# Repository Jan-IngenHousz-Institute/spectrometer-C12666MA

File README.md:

# C12666MA spectrometer

Hamamatsu C12666MA micro-spectrometer (340–780 nm, 256 pixels) read by a
Raspberry Pi Pico through an MCP3301 13-bit ADC, on the JII "C12666MA Board
v2". Includes a live GUI for chlorophyll fluorescence: it calculates relative
fluorescence from the incident-light region on a selected top spectrometer and
the fluorescence region on a selected bottom spectrometer, then plots the
ratio over time. Multiple spectrometers are synchronized for recordings of
minutes to days. A terminal recorder uploads the spectra to
an [openJII](https://openjii.org) experiment
([README_recorder.md](README_recorder.md)).

```
firmware/main.py      MicroPython firmware (copy to the Pico as main.py)
c12666ma/             Python package: driver, analysis, recorder, GUI, openJII upload and download
calibration/          pixel -> wavelength calibration and its laser measurements
tools/hw_check.py     speed / reliability / noise check of a connected board
tests/                unit tests (no hardware needed)
notebooks/            K. Tolsma's measurement and PAM notebooks, and a Digilent WaveForms test
kicad/                PCB v2, two variants: Pico on the back / on the front
legacy/arduino/       earlier Arduino Uno sketches, incl. the MCP3301 bench test
legacy/python-v1/     the first MicroPython firmware (MAIN.py) and playground notebooks
```

## Quick start

```
pip install -r requirements.txt
python -m c12666ma                 # the GUI
python -m c12666ma --simulate 3    # try it with three simulated spectrometers
```

1. Spectrometers plugged in are connected at start-up; later ones with
   **Auto-detect & connect**. Select one in the table to set its name, gain,
   integration time, averages and LED.
2. **Start**. With one spectrometer, "As fast as possible" streams one
   spectrum per integration time (about 190 spectra/s at the 5.2 ms minimum).
   Otherwise all spectrometers take one spectrum together at every period (see
   below).
3. Cover the sensors or switch the light off and press **Take dark**. The
   yield needs a dark spectrum taken with the same gain, integration time and
   averages, and the table shows when one no longer matches ("redo").
4. Drag the blue (`incident_light`) and red (`fluorescence`) regions, or type
   their limits. They apply to all spectrometers.
   Select the top (incident-light) and bottom (fluorescence) scanners in the
   controls below the live graph; both need matching dark spectra.
5. The **3D spectrum history** tab shows the most recent spectra of the
   selected spectrometer as a surface over wavelength, time and counts. It
   keeps up to 5000 spectra per spectrometer in memory, can show the latest
   2–500, and updates while it is open.
6. **Start recording**, optionally with a duration. It runs until stopped or
   for days; a new file part starts every 24 h (adjustable).

`run_C12666MA_3D_GUI.py` starts the GUI from any folder:

```
python path\to\spectrometer-C12666MA\run_C12666MA_3D_GUI.py
```

### Several spectrometers

All spectrometers take a spectrum together at every tick. The PC sends each
trigger up to 0.5 s ahead, with the start time converted to that device's
own clock. The clocks are measured every 30 s (offset and crystal drift), so
the devices should start within about a millisecond even when the PC
stalls. Spectra of the same tick have the same `seq` in every file.

- **Minimum period:** set by the slowest spectrometer, its averages ×
  integration time plus about 12 ms (readout and margins). The GUI shows
  which one.
- **Different integration times:** the windows are centred on the same
  moment; a 10 ms spectrum is taken in the middle of a 1 s one.
- **Unplugged or reset devices** are reconnected automatically (by their
  unique ID) and the recording continues; gaps show up as missed ticks.
- **Long recordings:** the PC is kept awake while recording, and the
  recording stops cleanly (with a note) if less than 500 MB of disk is left.

### Rel. fluo. yield

The live GUI calculates `bottom fluorescence / top incident_light` from
dark-subtracted sums in the selected wavelength regions. It combines readings
only when both scanners have the same synchronized frame sequence number. A
region "has signal" when its sum is more than *k* × its noise (k = 5 by
default; the noise comes from that scanner's dark frames). Both scanners need
a matching dark spectrum. The per-scanner `rel_fluo_yield` values in recording
files remain calculated from each individual spectrometer.

| Top incident_light | Bottom fluorescence | result |
|---|---|---|
| signal | any | bottom fluorescence / top incident_light |
| no signal | signal | empty + warning *fluorescence without incident light* |
| no signal | no signal | 0 |

Frames with a pixel at saturation in either region are flagged (orange in
the plot, `;saturated` in the file). The saturation level is about 3100
counts at high gain and about 1950 at low gain; both can be adjusted in the
GUI.

### Recording format

Each recording is a folder named `<name>_<date>_<time>`:

```
SIM-1_000001_part001.csv    one series per spectrometer (<name>_<end of its ID>),
SIM-1_000001_part002.csv    a new part every 24 h
SIM-2_000002_part001.csv
session.json                devices, settings, calibrations, counts, why it stopped
events.log                  connections, reconnects, settings changes, ...
```

Open a part with `pandas.read_csv(path, comment="#")`. The header lines
(`# ...`) hold the settings, regions and calibration. The `kind` column
separates the row types:

- `wavelength_nm`: the wavelength of every pixel column `px0..px255`
- `dark` / `dark_std`: the dark reference (written whenever one is taken, and
  repeated at the top of every part)
- `spectrum`: one row per spectrum, with the timestamp (start of
  integration), `t_s` (seconds since the recording started, the same time base
  for all spectrometers), `seq` (the tick number), settings, optionally
  `incident_light`, `fluorescence`, `rel_fluo_yield`, `yield_status`, and the
  raw counts (not dark-subtracted).

### Unattended recording with upload to openJII

`python -m c12666ma.record` records with all connected spectrometers from
the terminal, for hours or days, and sends the spectra to an experiment on
[openJII](https://openjii.org) as an *upload table*. Each unit keeps its own
gain, integration time and averages.

```
python -m c12666ma.record                 asks everything: sign-in, experiment, settings
python -m c12666ma.record login           (re)enter the openJII API key
python -m c12666ma.record upload FOLDER   finish the uploads of an earlier recording
python -m c12666ma.download               download all tables of an experiment into one JSON file
```

The spectra are written locally first (the recording folder described above)
and uploaded every 15 minutes, one row per spectrum with its timestamp and
settings. Without network they wait on disk and go out later.
**[README_recorder.md](README_recorder.md)** explains the whole procedure:
sign-in, laptop settings for runs of several days, the uploaded columns,
starting from Task Scheduler, downloading the data again and troubleshooting.

# Recording to openJII from the terminal

`python -m c12666ma.record` records with every C12666MA spectrometer plugged
into the laptop, one spectrum per unit at a fixed interval, for hours or days.
Each unit can have its own gain, integration time and averages. Every spectrum
is saved on the laptop first and then uploaded to an experiment on
[openJII](https://openjii.org), with its timestamp and all the settings it was
taken with.

No GUI is needed: the script asks its questions in the terminal, and remembers
the answers for the next run.

- [Before you start](#before-you-start)
- [First recording, step by step](#first-recording-step-by-step)
- [Leaving it running for days](#leaving-it-running-for-days)
- [Stopping, and finishing the uploads](#stopping-and-finishing-the-uploads)
- [What is saved](#what-is-saved)
- [Starting without questions](#starting-without-questions)
- [Troubleshooting](#troubleshooting)

## Before you start

1. **Python** 3.12 or 3.13, with the packages of this repository:

   ```
   pip install -r requirements.txt
   ```

   Run every command below from the repository folder (the one with this file).

2. **Firmware v2.1 on every Pico.** Copy `firmware/main.py` to the Pico as
   `main.py` (see the main [README](README.md#firmware)). The script refuses
   older firmware.

3. **A name and a calibration per unit.** Units are recognised by their unique
   ID and shown by the name stored on the device (set it once in the GUI,
   `python -m c12666ma`). A unit without its own wavelength calibration still
   records, with a warning: its wavelengths are those of another unit (see
   [Wavelength calibration](README.md#wavelength-calibration)).

4. **An openJII account and an experiment** you are a member of. To upload into
   an existing table you need *contribute* access. To create a new table, which
   the first upload does, you need *manage* access (experiment admin).

5. **Close the GUI, Thonny or anything else** that has the spectrometers' COM
   ports open. A port can only be used by one program at a time.

## First recording, step by step

Plug in the spectrometers and run:

```
python -m c12666ma.record
```

The script goes through four steps. Press Enter to accept the value in
`[brackets]`.

**1. Sign in to openJII.** The first time, the script opens
*Account > API keys* on openJII in the browser. Create a personal key there,
copy it and paste it into the terminal; it is not shown while you paste. The
key is checked and stored in your Windows profile, so later runs skip this
step.

```
Sign in to openJII (prod): create a personal API key at
  https://openjii.org/en-US/platform/account/api-keys
Open that page in the browser? (y/n) [y]:
Paste the API key (hidden):
openJII (prod): signed in as John Doe
```

**2. Choose the experiment and the table.** Pick a number from the list of your
active experiments, or choose the last entry and paste the experiment's link
from the browser. The spectra go into an *upload table* of that experiment;
keep the default name unless you want separate tables.

```
Active experiments you are a member of:
   1. test-experiment  (5db72a32-1c50-4d11-b12c-0152cc65b5e6)
   2. another one (paste its id or URL)
Record into experiment: 1
Upload table name in the experiment [c12666ma_spectra]:
Experiment: test-experiment  (https://openjii.org/en-US/platform/experiments/5db72a32-...)
Table: c12666ma_spectra (will be created)
```

**3. Set each spectrometer.** Every unit found on USB is listed, then asked for
its gain (`high` or `low`), integration time in milliseconds, number of
averages (1 to 16) and whether its LED is on. The units can have different
settings.

```
2 spectrometer(s):
  Fluor      COM42  id E664B012CF234E35  gain high  integration 100 ms  averages 1  LED off
  Top        COM7   id E663589863441E2E  gain high  integration 50 ms  averages 2  LED off

Fluor on COM42 (id E664B012CF234E35)
  gain (high/low) [high]:
  integration time in ms [100.0]:
  averages (1-16) [1]:
  LED on during the recording? (y/n) [n]:
```

**4. Timing and files.**

| Question | What it means |
|---|---|
| Period between spectra in seconds | All units take one spectrum together at every period. The minimum shown depends on the slowest unit: its averages × integration time, plus about 12 ms. |
| Upload to openJII every | How often the new spectra are sent. 15 minutes is a good default; the minimum is 1 minute. |
| Local folder for the recording | Where the files are written. Each recording gets its own subfolder. Default: `C12666MA data` in your user folder. |
| Duration | For example `36h` or `3d`. `0` records until you press Ctrl-C. |
| Note for the file header | Free text saved with every spectrum, e.g. the plant or the chamber. |
| Take a dark spectrum first? | Optional. Cover the sensors when asked; 20 dark frames per unit are recorded and uploaded as `dark` rows. |

The recording then starts. Every minute a status line shows what has been
measured and uploaded:

```
Recording to C:\Users\you\C12666MA data\test-experiment_2026-10-28_22-16-18
Period 60 s, upload every 15m, until Ctrl-C

22:17:18 · tick 7 · Fluor 6 · Top 6 · 12 spectra on disk · uploads 0 confirmed, 1 waiting
2026-10-28T22:17:20+01:00  upload: sent 1 batch(es), 12 rows, upload 7d8098da
2026-10-28T22:18:24+01:00  upload 7d8098da: 12 rows queryable on openJII
```

The spectra appear in the experiment's data on openJII about a minute after
each upload. A new table is listed in the experiment a few minutes after its
first upload. Until then the next uploads wait and retry every minute; the
terminal says *the table is not listed on the platform yet*, which is normal.

## Leaving it running for days

The script keeps the laptop awake while it records, reconnects units that were
unplugged or reset, and starts a new local file every 24 hours. Windows can
still interrupt it, so before a long run:

- **Connect the charger.**
- **Closing the lid:** set *Control Panel > Power Options > Choose what closing
  the lid does* to *Do nothing* when plugged in, or leave the lid open.
- **Windows Update:** pause updates for the length of the run (*Settings >
  Windows Update > Pause updates*). An update restart stops the recording.
- **USB power saving:** in *Power Options > Change plan settings > Change
  advanced power settings*, set *USB settings > USB selective suspend setting*
  to *Disabled*.
- **Don't select text in the terminal window.** In the classic Windows
  console, a selection pauses the program until you press Esc.
- **Disk space:** the recording stops cleanly, with a note in the log, when
  less than 500 MB is left on the disk.

Network outages don't matter. The spectra keep being written to disk, the
status line shows *OFFLINE, keeping local*, and everything that was missed is
uploaded once the connection is back.

Two units at one spectrum per minute use about this much disk space:

| | Per day |
|---|---|
| Local CSV files | about 4 MB |
| Upload batches, kept in `uploads\` | about 10 MB |

## Stopping, and finishing the uploads

Press **Ctrl-C once**. The script sends the spectra not uploaded yet, waits up
to a few minutes for openJII to confirm them, and then tells you whether
anything is left:

```
Stopping (Ctrl-C)...
Uploading the last batch and waiting for the platform's confirmation...
Uploads: {'completed': 96}
Local files: C:\Users\you\C12666MA data\test-experiment_2026-10-28_22-16-18  (2880 spectra)
```

If the network was down, or the laptop crashed or restarted during a
recording, send what is left later with the folder of that recording:

```
python -m c12666ma.record upload "C:\Users\you\C12666MA data\test-experiment_2026-10-28_22-16-18"
```

This also recovers the spectra written just before a crash. Running it on a
recording that is already fully uploaded does nothing, so it is always safe.

A restarted laptop does not resume the recording by itself. Start a new
recording; it goes into a new folder, and you finish the old folder's uploads
with the command above.

## What is saved

### On the laptop

Each recording folder holds:

```
Fluor_234E35_part001.csv   spectra of one unit (<name>_<end of its ID>), a new part every 24 h
Top_441E2E_part001.csv
session.json               units, settings, calibrations, number of spectra, why it stopped
events.log                 connections, reconnects, uploads, errors
uploads\                   the batches sent to openJII and their status (ledger.json)
```

The CSV format is described in the main
[README](README.md#recording-format). Open a part with
`pandas.read_csv(path, comment="#")`.

### On openJII

Each spectrum is one row in the experiment's upload table, by default
`c12666ma_spectra`. Every row describes itself completely:

| Column | Content |
|---|---|
| `kind` | `spectrum`, or `dark` for a dark reference |
| `timestamp_utc`, `timestamp_local`, `unix_time` | start of the integration |
| `t_s` | seconds since the recording started, the same time base for all units |
| `tick` | measurement number; spectra with the same tick were taken together |
| `session_id` | the recording folder name |
| `note` | the note entered at the start |
| `device_uid`, `device_name`, `port`, `firmware` | which unit took it |
| `integration_ms`, `integration_us`, `n_avg` | integration time and number of averages |
| `gain`, `high_gain` | `high` or `low` |
| `led` | whether the unit's LED was on |
| `flags`, `flag_names`, `adc_errors` | quality flags of the frame, e.g. `late` or `led_changed` |
| `clk_hz`, `n_pixels` | sensor clock and number of pixels (256) |
| `wavelength_coeffs`, `wavelength_nm` | the unit's calibration, and the wavelength of every pixel |
| `counts` | the 256 raw values, not dark-subtracted |

Dark rows hold `counts_mean` and `counts_std` instead of `counts`, plus the
number of frames averaged in `n_frames`.

## Starting without questions

Every question has a flag. With `--yes` the script asks nothing and uses the
flags, then the answers remembered from the last run. This is how to start it
from a batch file or from Windows Task Scheduler.

```
python -m c12666ma.record --yes --experiment "test-experiment" --table c12666ma_spectra ^
    --device Fluor=high,100,1 --device Top=low,50,4,on --period 60 --upload-every 15m ^
    --duration 5d --folder "D:\spectra" --note "chamber 2"
```

| Flag | Meaning |
|---|---|
| `--experiment` | experiment ID, link, or exact name |
| `--table` | upload table name (default `c12666ma_spectra`) |
| `--device NAME=gain,ms,averages[,on]` | settings of one unit, by name or ID; repeat for each unit |
| `--all gain,ms,averages[,on]` | the same settings for every unit |
| `--period` | seconds between spectra |
| `--upload-every` | e.g. `15m`, `1h` |
| `--folder`, `--prefix` | where to record, and the start of the folder name (default: the experiment name) |
| `--duration` | e.g. `36h`, `3d`; without it, until Ctrl-C |
| `--note` | note saved with every spectrum |
| `--dark [N]` | take N dark frames per unit first (default 20). With `--yes` it measures straight away, without asking you to cover the sensors. |
| `--part-hours` | hours per local file part (default 24) |
| `--no-upload` | record on the laptop only |
| `--env dev` | use the openJII development platform instead of openjii.org |

`--yes` needs a stored API key. Run `python -m c12666ma.record login` once
first.

**Task Scheduler:** create a task with the action *Start a program*. Set
*Program* to the full path of `python.exe`, *Arguments* to everything after
`python` in the command above, and *Start in* to the repository folder.

## Troubleshooting

| Message | What to do |
|---|---|
| `no spectrometer found on USB` | Check the cables, and close the GUI or Thonny if they are open. |
| `firmware too old` | Copy `firmware/main.py` to that Pico. |
| `warning: Top has no calibration of its own` | The unit records with another unit's wavelengths. Calibrate it when possible. |
| `your account cannot contribute data` | Ask the experiment's admin to add you as a member. |
| `table ... does not exist ... (needs manage access)` | Ask an admin to make the first upload, or use a table name that already exists. |
| `no valid openJII API key` | No key is stored, or openJII no longer accepts it. Run `python -m c12666ma.record login`. |
| `the table is not listed on the platform yet` | Normal for a new table during its first minutes. The upload retries by itself. |
| `OFFLINE, keeping local` in the status line | No connection to openJII. Nothing to do: the uploads catch up later. |
| `LOST` next to a unit in the status line | The unit was unplugged or reset. It is reconnected automatically; the gap shows as missed ticks. |
| `upload ... FAILED on the platform` | openJII refused that batch and it is not resent. The spectra are still in the local CSV files and in `uploads\`. Report the upload ID shown. |

**The stored key and answers** are in `%APPDATA%\c12666ma\openjii.json`. To use
another key or account, run `python -m c12666ma.record login`. If the laptop
is shared or lost, delete the key on openJII under *Account > API keys*.

### Scripting

```python
from c12666ma import Spectrometer

with Spectrometer.open() as spec:          # finds the Pico automatically
    spec.set_integration_us(20_000)
    frame = spec.read_frame()              # frame.counts: 256 values
    spec.start_stream(period_us=0)
    frame = spec.frames.get()              # frames keep arriving until stop_stream()
    spec.stop_stream()
```

## Firmware

Copy `firmware/main.py` to the Pico as `main.py`, with Thonny or with
`mpremote cp firmware/main.py :main.py`. The serial protocol is documented
at the top of the file. Commands are text lines (`set_integration,20000`,
`spec,raw`, ...), and the v1 commands still work. Settings stay in RAM until
you send `save`. Synchronised acquisition needs firmware v2.1 (`idn`); the
GUI says so if a device has an older one.

The sensor clock (200 kHz), the start pulses and the ADC conversions are
generated by the Pico's PIO state machines, and DMA moves the samples to RAM.
The readout therefore doesn't depend on Python timing. Per the datasheet,
the integration time is the interval between start pulses, so it is exactly
N clocks for every pixel. Readout overlaps the next integration, so
streaming has no dead time.

Measured on the board in October 2026 (`python tools/hw_check.py`, 60 s
run):

| | |
|---|---|
| frame rate at the 5.175 ms minimum integration | 193.2 spectra/s, period exact to 1 µs |
| dropped frames / checksum errors / ADC framing errors | 0 / 0 / 0 (11 593 frames) |
| device CPU load at that rate | 48 % |
| dark noise | ~11 counts rms per pixel (old firmware: same median, but outliers up to 350) |

The noise floor (~11 mV rms) is set by the analog front end, not the sensor
(datasheet readout noise 0.5 mV).

## Wavelength calibration

There is no Hamamatsu inspection sheet for this unit, so
`calibration/fit_wavelength.py` fits a weighted quadratic to:

- a green (532.0 nm) and a red (650 nm) laser pointer (`calibration/*_laser.csv`);
- the chlorophyll fluorescence peaks (685 / ~737 nm) in 13 leaf recordings,
  which constrain the curvature and the red end.

The fit:

    nm = 327.15 + 2.54396·p − 0.0024563·p²     (p = pixel 0..255)

Expect about ±1 nm near 532 nm and a few nm up to 745 nm. Below 532 nm the
curve is extrapolated, so a blue line would improve it: a violet (405 nm)
laser, or a fluorescent lamp (Hg lines at 404.7 / 435.8 / 546.1 nm).

`calibration/wavelength_calibration.json` is the reference. When the GUI
connects, it writes these coefficients to the device's flash if the device
holds different ones. Scripts can read them back with `get_wl_coeffs`.

Every sensor needs its own calibration. A calibration file applies to the
unit whose ID is in its `unit_uid` field (the ID is in `status` and in the
GUI). Save a new unit's fit as `calibration/wavelength_calibration_<name>.json`
with its `unit_uid`. A unit without its own file is shown with another unit's
calibration, marked "approximate", and that calibration is not written to it.

## Hardware notes (board v2)

- MCP3301 DOUT (5 V logic) is wired straight to GP16. The RP2040 is not 5 V
  tolerant. For the next revision, add a divider or a 3.3 V buffer; a
  ~2.2 kΩ series resistor is the quick fix.
- The video output reaches the ADC through 5 kΩ with no buffer amplifier (the
  datasheet recommends a CMOS op-amp buffer). This limits the ADC clock and
  probably adds noise.
- GP15 (the LED / excitation light) is not routed on the PCB and has to be
  wired separately.
- The schematic uses JII library symbols ("Library JII") that are embedded
  in the files but not included as a library.

## Development

```
python -m pytest                       # unit tests (simulated spectrometers, no hardware)
python tools/hw_check.py               # with a board connected
python -m c12666ma --simulate 3        # the GUI with simulated spectrometers
python calibration/fit_wavelength.py   # re-fit the calibration (the GUI copies it to the device)
```

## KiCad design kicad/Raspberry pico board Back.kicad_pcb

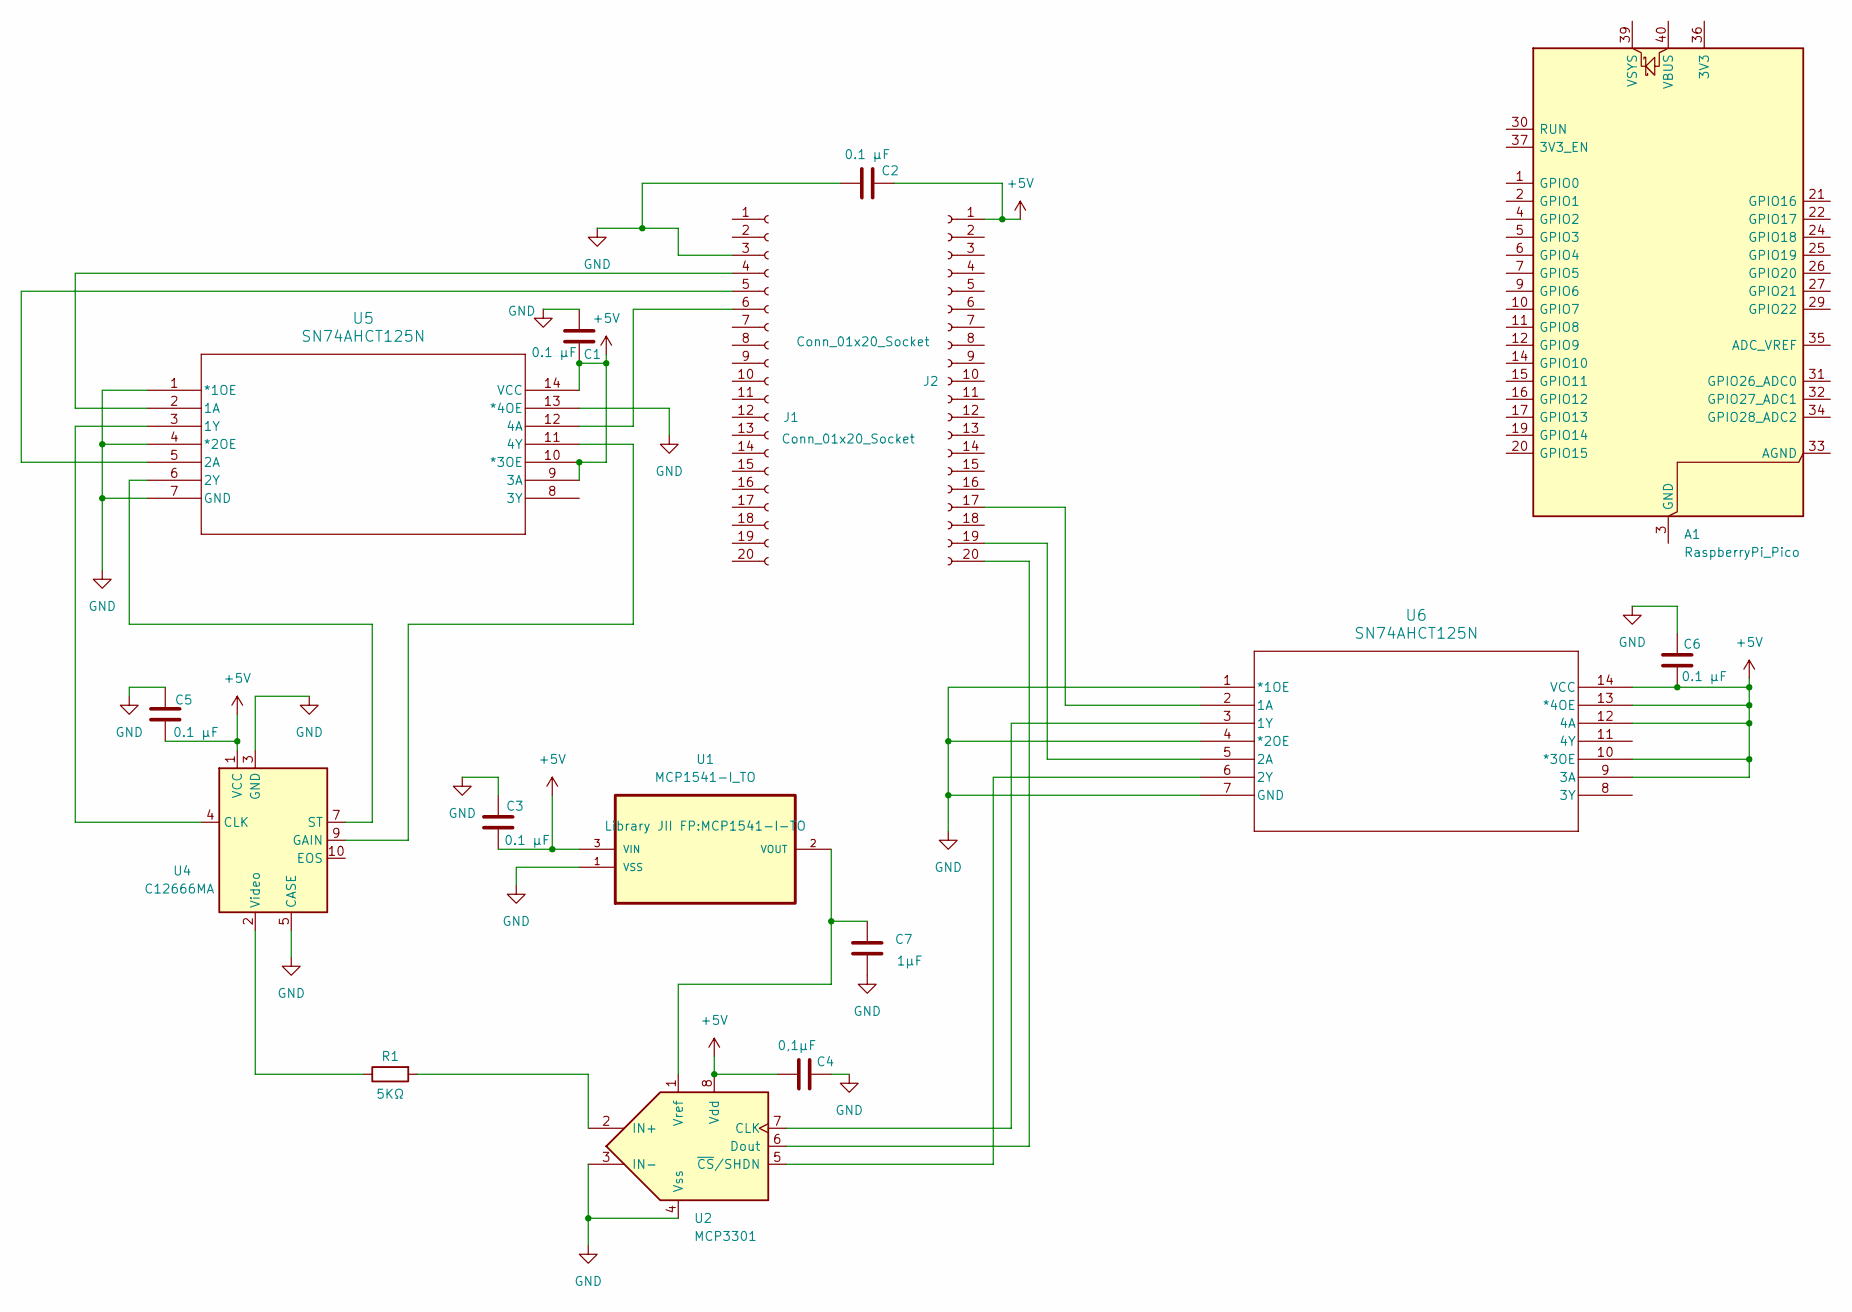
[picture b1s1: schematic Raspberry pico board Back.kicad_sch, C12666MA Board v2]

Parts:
A1: RaspberryPi_Pico; RaspberryPi_Pico_Common_Unspecified
C1, C2, C3, C5, C6: 0.1 μF; C_0805_2012Metric_Pad1.18x1.45mm_HandSolder
C4: 0,1μF; C_0805_2012Metric_Pad1.18x1.45mm_HandSolder
C7: 1μF; C_0805_2012Metric_Pad1.18x1.45mm_HandSolder
J1, J2: Conn_01x20_Socket; PinHeader_1x20_P2.54mm_Vertical
R1: 5KΩ; R_0805_2012Metric_Pad1.20x1.40mm_HandSolder
U1: MCP1541-I_TO; MCP1541-I-TO; MPN MCP1541-I/TO
U2: MCP3301; MCP3301_BI_P
U4: C12666MA; Hamamatsu_C12880
U5, U6: SN74AHCT125N

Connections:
+5V: C1.2, C2.2, C3.2, C4.1, C5.2, C6.2, J2.1, U1.3 (VIN), U2.8 (Vdd), U4.1 (VCC), U5.9 (3A), U5.10 (*3OE), U5.14 (VCC), U6.9 (3A), U6.10 (*3OE), U6.12 (4A), U6.13 (*4OE), U6.14 (VCC)
GND: C1.1, C2.1, C3.1, C4.2, C5.1, C6.1, C7.2, J1.3, U1.1 (VSS), U2.3 (IN-), U2.4 (Vss), U4.3 (GND), U4.5 (CASE), U5.1 (*1OE), U5.4 (*2OE), U5.7 (GND), U5.13 (*4OE), U6.1 (*1OE), U6.4 (*2OE), U6.7 (GND)
unnamed: A1.3 (GND), A1.8 (GND), A1.13 (GND), A1.18 (GND), A1.23 (GND), A1.28 (GND), A1.38 (GND)
unnamed: J1.4, U5.2 (1A)
unnamed: J1.5, U5.5 (2A)
unnamed: J1.6, U5.12 (4A)
unnamed: J2.17, U6.2 (1A)
unnamed: J2.19, U6.5 (2A)
unnamed: J2.20, U2.6 (Dout)
unnamed: C7.1, U1.2 (VOUT), U2.1 (Vref)
unnamed: U2.7 (CLK), U6.3 (1Y)
unnamed: R1.2, U2.2 (IN+)
unnamed: U2.5 (~CS/SHDN), U6.6 (2Y)
unnamed: U4.4 (CLK), U5.3 (1Y)
unnamed: U4.9 (GAIN), U5.11 (4Y)
unnamed: U4.7 (ST), U5.6 (2Y)
unnamed: R1.1, U4.2 (Video)

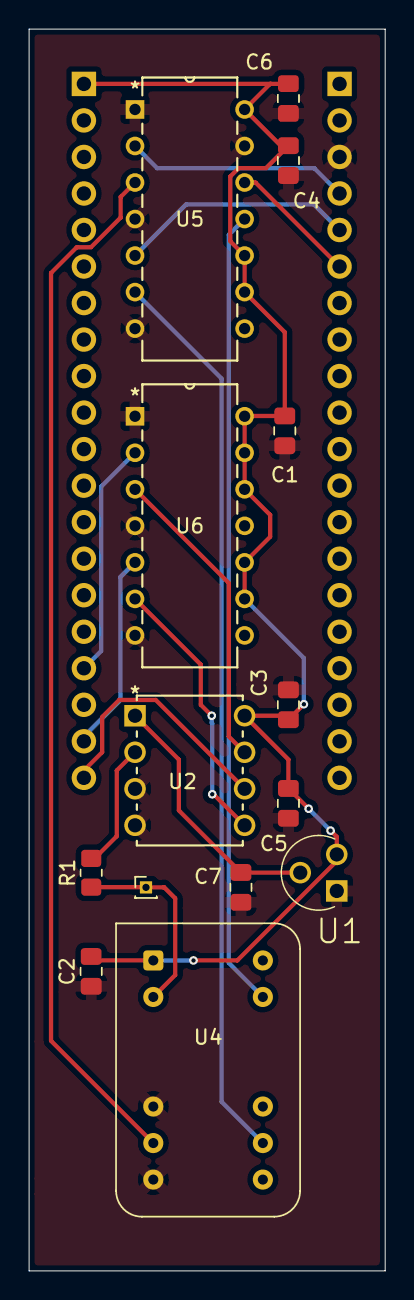
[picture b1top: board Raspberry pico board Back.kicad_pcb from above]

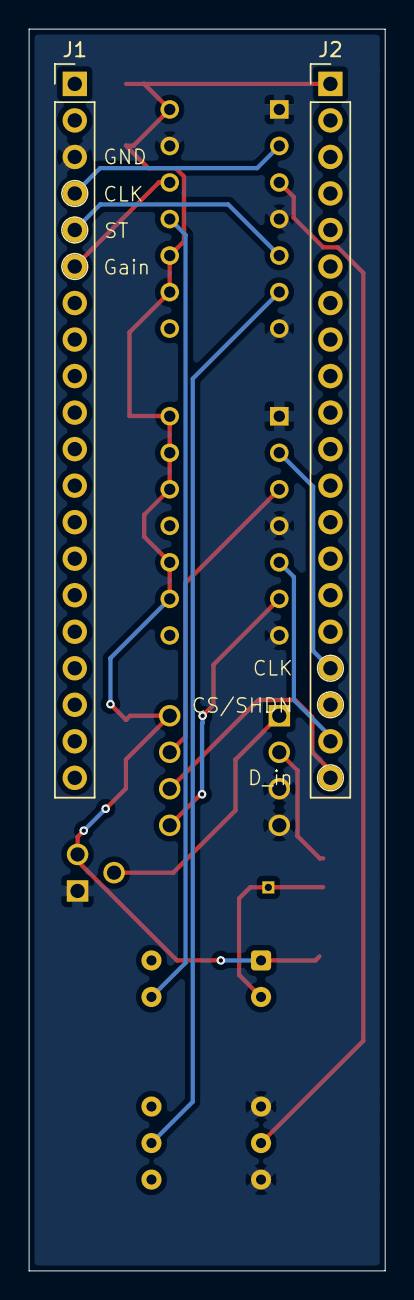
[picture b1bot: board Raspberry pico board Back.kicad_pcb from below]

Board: 2 copper layers, 24.8 x 86.4 mm, 15 parts (2 on the bottom side), 16 nets.
